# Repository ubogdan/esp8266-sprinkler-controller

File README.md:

# esp8266-sprinkler-controller
A Web based sprinkler controller using the ESP8266

Versions of software used:

Arduino IDE 1.6.5
Boards Manager: esp8266 by ESP8266 Community version 2.0.0
Library Manager: DallasTemperature by Miles Burton, Tim Newsome, Guil Barros, Rob Tillaart Version 3.7.5

Eagle 7.5.0 Light (Free Version)

I used an ESP-03 module in this project, but if you want to get the OTA firmware update to work you need to use a module with more flash memory. (It works just fine without OTA updates)

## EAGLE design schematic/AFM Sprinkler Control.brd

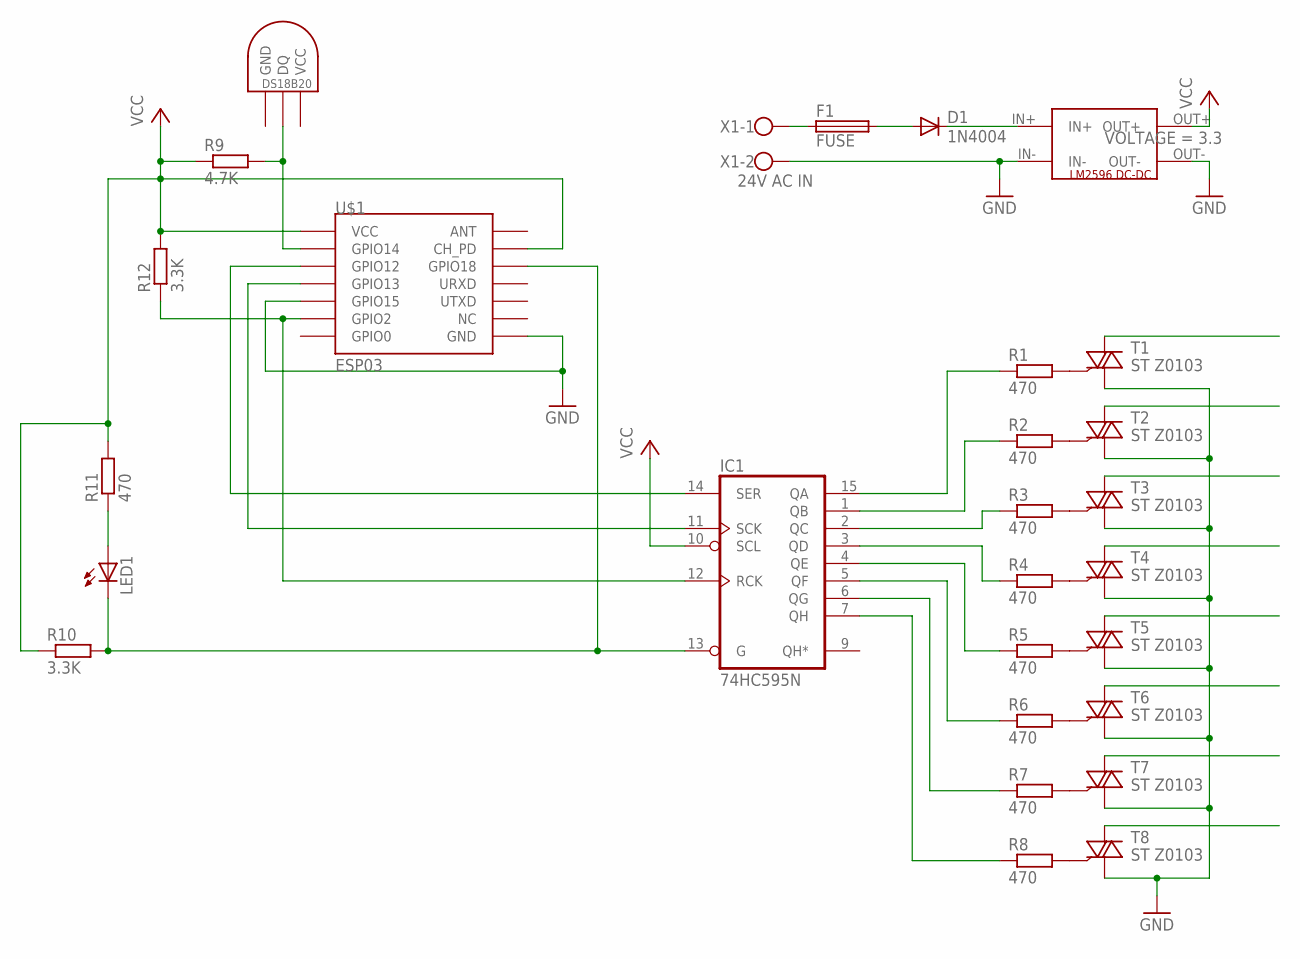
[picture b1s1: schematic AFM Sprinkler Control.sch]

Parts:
D1: 1N4004; DO41-10
F1: FUSE; 19560
IC1: 74HC595N; DIL16
LED1: LED3MM
R1, R2, R3, R4, R5, R6, R7, R8: 470; 0204/5
R9: 4.7K; 0204V
R10: 3.3K; 0204/7
R11: 470; 0207/10
R12: 3.3K; 0204/5
T1, T2, T3, T4, T5, T6, T7, T8: ST Z0103; TO92-AFM
U$1: ESP03; ESP03-BREAKOUT
U$2: LM2596MOD-ADJ; VOLTAGE 3.3
U$3: DS1820TO92; DS1820
X1: 24V AC IN; W237-102

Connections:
24VAC: F1.1, X1.1
GND: IC1.8 (GND), T1.T1 (A1), T2.T1 (A1), T3.T1 (A1), T4.T1 (A1), T5.T1 (A1), T6.T1 (A1), T7.T1 (A1), T8.T1 (A1), U$1.GND, U$1.GPIO15, U$2.IN-, U$2.OUT-, U$3.GND, X1.2
unnamed: R1.2, T1.G
unnamed: R2.2, T2.G
unnamed: IC1.2 (QC), R3.1
unnamed: LED1.A, R11.1
unnamed: D1.A, F1.2
unnamed: D1.C, U$2.IN+
unnamed: R3.2, T3.G
unnamed: R4.2, T4.G
unnamed: R5.2, T5.G
unnamed: R6.2, T6.G
unnamed: R7.2, T7.G
unnamed: R8.2, T8.G
unnamed: IC1.1 (QB), R2.1
unnamed: IC1.15 (QA), R1.1
unnamed: IC1.3 (QD), R4.1
unnamed: IC1.4 (QE), R5.1
unnamed: IC1.5 (QF), R6.1
unnamed: IC1.6 (QG), R7.1
unnamed: IC1.7 (QH), R8.1
unnamed: IC1.14 (SER), U$1.GPIO12
unnamed: IC1.11 (SCK), U$1.GPIO13
unnamed: IC1.12 (RCK), R12.1, U$1.GPIO2
unnamed: R9.2, U$1.GPIO14, U$3.DQ
unnamed: IC1.13 (G), LED1.K (C), R10.2, U$1.GPIO18
VCC: IC1.10 (SCL), IC1.16 (VCC), R9.1, R10.1, R11.2, R12.2, U$1.CH_PD, U$1.VCC, U$2.OUT+, U$3.VDD (VCC)

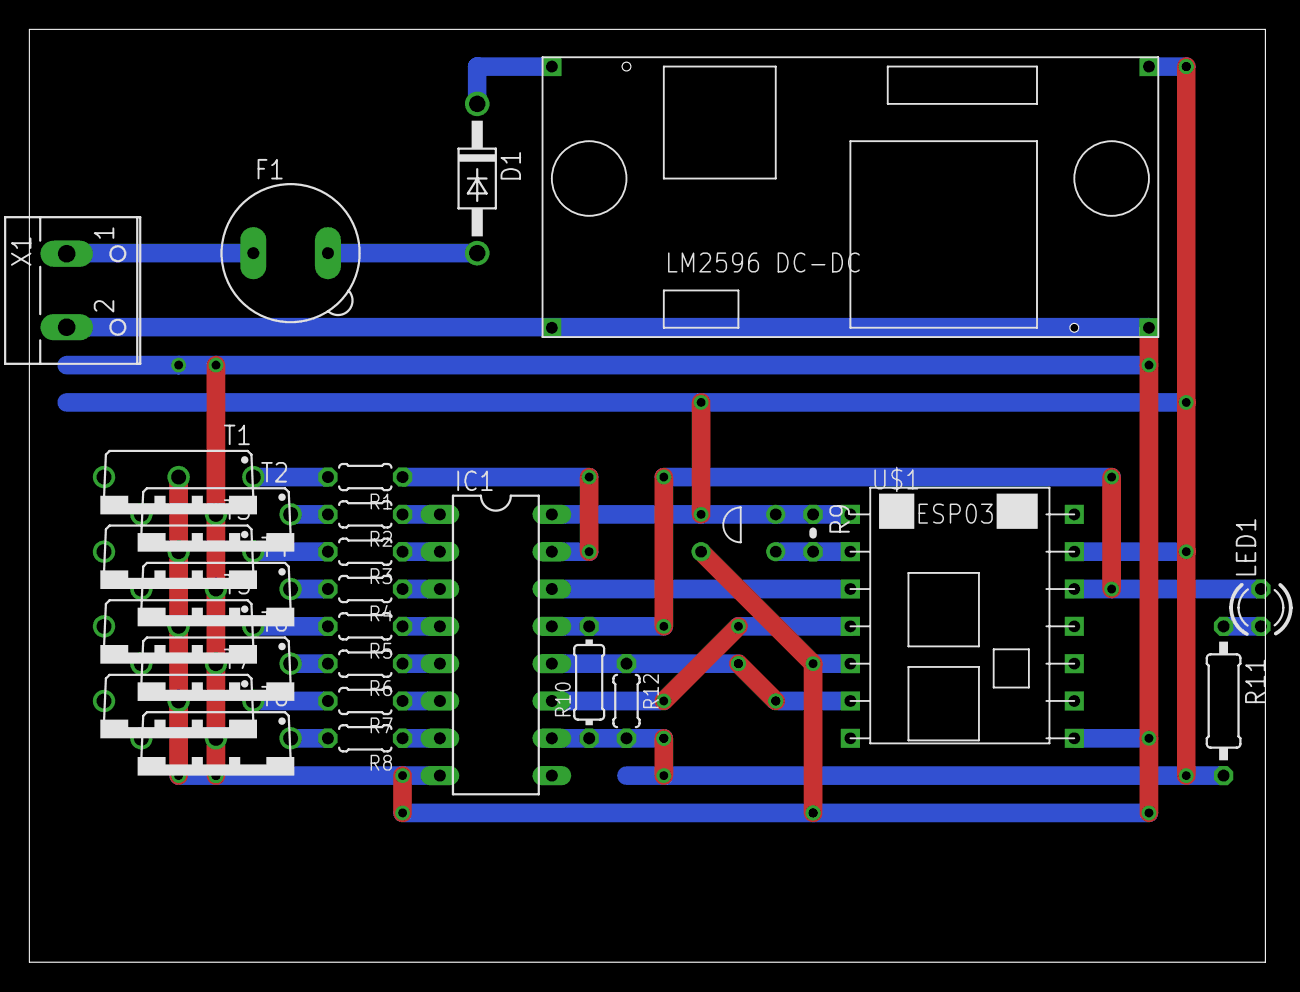
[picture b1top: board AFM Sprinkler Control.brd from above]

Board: 2 copper layers, 84.1 x 63.5 mm, 28 parts (0 on the bottom side), 27 nets.

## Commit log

2016-03-11 Added files via upload
